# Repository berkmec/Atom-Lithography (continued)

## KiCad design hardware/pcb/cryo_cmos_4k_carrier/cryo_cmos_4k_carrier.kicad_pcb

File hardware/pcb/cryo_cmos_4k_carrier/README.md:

# Cryo-CMOS `4 K` Carrier (`968`-Gate SKY130 Crossbar Mux + `4 K / MXC` RC/Eccosorb Filter) & Live `ngspice-47` Verification

**BOM Coverage:** `S6.10-03`, `S6.7-02`, `S7.3-02`, `S7.3-01`  
**Epistemic Status:** `M0/M1_DESIGN_ONLY` — `no_lab_measurement=true`, `no_physical_fab=true`, `iec61508_certified=false`, `semi_s2_certified=false`. Active COTS connectors are `{Aday-COTS}`; SKY130 `4 K` dies and Eccosorb CR-124 RF absorber blocks are `{Ozel-Uretim}`.

## 1. `4 K` 4-Layer Cryo-CMOS Carrier Architecture (`cryo_cmos_4k_carrier.{kicad_sch,kicad_pcb}`)

- **Dimensions & Stackup:** `165 × 125 mm`, **`4` copper layers**, `1.478 mm` total thickness, thermal-cycle-hardened (`>100` cooldowns `300 K ↔ 4 K`):
  - Outer ENIG Au wire-bondable layers (`F.Cu`, `B.Cu`) over `0.254 mm` **Rogers RO4350B** (`ε_r = 3.48`).
  - Central `0.800 mm` **AlN / Cu-Invar-Cu CTE-matched core** (`ε_r = 8.90`, `CTE ≈ 4.5 ppm/K` matched to Si) sandwiched between `In1.Cu` (`GND_4K`) and `In2.Cu` (`VDD_4K_1V2`).
- **Thermal Isolation Split (`OBS-019`):** `4 K` (`GND_4K`, `x ≤ 112 mm`, `J_THERM_4K_A/B`) and `20 mK` MXC (`GND_MXC`, `x ≥ 118 mm`, `J_THERM_MXC`, `R2_MXC`/`C2_MXC`/`J_MXC_GATE_A/B`) copper planes are physically split across a `6.0 mm` copper-free thermal break moat (`5.0 mm` multi-layer `THERMAL_ISOLATION_4K_TO_MXC` keepout), eliminating the `~34.8 mW` unbroken copper plane thermal short; full dilution-fridge build mounts Stage-2 on a separate MXC daughterboard via NbTi/manganin Eccosorb harnesses.
- **`968`-Gate SKY130 `4 K` Crossbar Mux (`S6.10-03`, `S7.3-01`, `S7.3-02`, `OBS-091` / `OBS-135`):**
  - Hosts `8×` SKY130 `121`-gate cryo-CMOS crossbar mux dies (`U_MUX0..U_MUX7` = `968` local Stark/M4/SET DC gates for the `Exp131` `L = 11` surface code: `121` nodes × `8` DC gates/node; `8` representative bank outputs routed to the filter array).
  - Real `0.635 mm` pitch Omnetics Bi-Lobe Nano-D connectors (`Connector_Omnetics:NanoD_2x4_P0.635mm`, G-S-G-S high-speed pinout); per-chip `100 nF C0G/NP0` decoupling on ALL 3 rails (`VDD_4K_1V2`, `VBIAS_POS_2V`, `VBIAS_NEG_2V`; zero Class-II X7R freeze-out); SKY130 `±2.0 V` (`4.0 V` span) gate-hold buffers require `5 V` thick-oxide (`g5v0d10v5`) triple-well devices tied to `-2.0 V` and `4 K` BSIM4 PDK verification at M2 (`NMOS_SKY4K`/`PMOS_SKY4K` in SPICE are `LEVEL=1` behavioral effective-`V_th` switches).
  - Controlled `50 Ω SE` SPI microstrips across ALL SPI nets INCLUDING daisy-chain hops `SPI_CHAIN_0_1..6_7` (`w = 0.5429 mm` → `Z0 = 50.00 Ω`, `193 / 193` DRC checks PASS, adjacent `GND_4K` stitching vias `< 3.5 mm` from every die).
- **`4 K / MXC (20 mK)` 2-Stage RC + Eccosorb CR-124 DC Gate Filter Bank (`S6.7-02`):**
  - `8` representative Stark/M4/SET filter channels (`R1 = 1.0 kΩ` NiCr + `C1 = 100 nF` C0G `|| 100 pF` HF shunt w/ `1.0 Ω` NiCr ESL-damping ESR at `4 K` → `Eccosorb CR-124` → `6.0 mm` thermal moat → `R2 = 2.0 kΩ` + `C2 = 47 nF` C0G `|| 100 pF` HF shunt on isolated `GND_MXC` at `20 mK`).
- **Strict EDA & Physical Copper Connectivity Verification:** `100` components, `54` nets, **`routed = 54 / 54` (`100%` pad-to-pad)**, **`unconnected_items = 0`**, **`track_dangling_count = 0`**, `782` copper segments, `251` vias, **`0` ERC errors**, **`0` DRC errors**, `SCH ↔ PCB` netlist parity PASS.

## 2. Live `ngspice-47` `4 K / 20 mK` Filter, Thermal Noise & Power Verification (`cryo_4k_gate_filter.cir`)

Executed natively with `ngspice-47 -b` (exit `0`, `0` errors, `0` warnings) using `.temp -269.15` (`4.00 K` global stage), per-instance `temp=-273.13` (`20 mK` MXC), and `temp=26.85` (`300 K` upstream DAC noise equivalent `7.50 nV/√Hz`), including realistic `0.05 pF` resistor body strays, `0.60 nH` MLCC ESLs with `1.0 Ω` HF damping ESR, and FULL bipolar `±2.0 V` (`+2.0 V` AND `-2.0 V` rail) power accounting:

| Metric | `ngspice-47` Measured | Independent Python MNA / Nyquist | Target / Spec | Status |
| :--- | :---: | :---: | :---: | :---: |
| Filter `-3 dB` Bandwidth `f_3dB` | `669.29 Hz` | — | Quasi-static DC Stark/SET | **PASS** |
| RF Attenuation `@ 1 GHz` (w/ `1.0 Ω` ESL damping) | **`-172.82 dB`** | `-172.83 dB` (`0.009 dB` diff) | `> 60 dB` (`≤ -60 dB`) | **PASS** |
| In-Band Total Noise `@ 10 Hz` (`300 K` DAC + `4 K` + `20 mK`) | **`7.523 nV/√Hz`** (`0.00752 µV/√Hz`) | `7.524 nV/√Hz` (`0.01%` parity) | `< 0.5 µV/√Hz` | **PASS** |
| Intrinsic `4 K + 20 mK` Filter-Only Thermal Noise `@ 10 Hz` | **`0.5275 nV/√Hz`** | `0.5276 nV/√Hz` (`0.02%` parity) | Cryogenic Nyquist floor | **PASS** |
| Total Integrated Output RMS Noise (`1 Hz – 1 MHz`) | **`0.2251 µVrms`** | — | Sub-µVrms Stark/SET stability | **PASS** |
| `0 → 1.0 V` Stark Step `10–90%` Rise / `0.1%` Settling Time | `520.2 µs` / **`1.632 ms`** | — | Clean settling `< 5 ms` | **PASS** |
| `968`-Gate SKY130 `4 K` Total Power (incl. `+2 V` & `-2 V` rails) | **`13.636 mW`** (`2.808` core/dyn + `5.414` `+2 V` + `5.414` `-2 V`) | — | **`≤ 15.4 mW @ 4 K`** | **PASS** |

*\*Epistemic caveat:* Lumped SPICE models assume an ideal Faraday partition between the `4 K` and `20 mK` filter bays; physical cryogenic enclosure cavity crosstalk typically floors practical measured RF isolation near `100–120 dB`, still providing `40–60 dB` margin beyond the `> 60 dB @ 1 GHz` requirement.

## 3. Reproducibility

```bash
PYTHONPATH=.:src python -B hardware/pcb/cryo_cmos_4k_carrier/build_cryo_4k_carrier.py
PYTHONPATH=.:src pytest tests/test_pcb_fpga_blanker_cryo.py -v -p no:cacheprovider
```

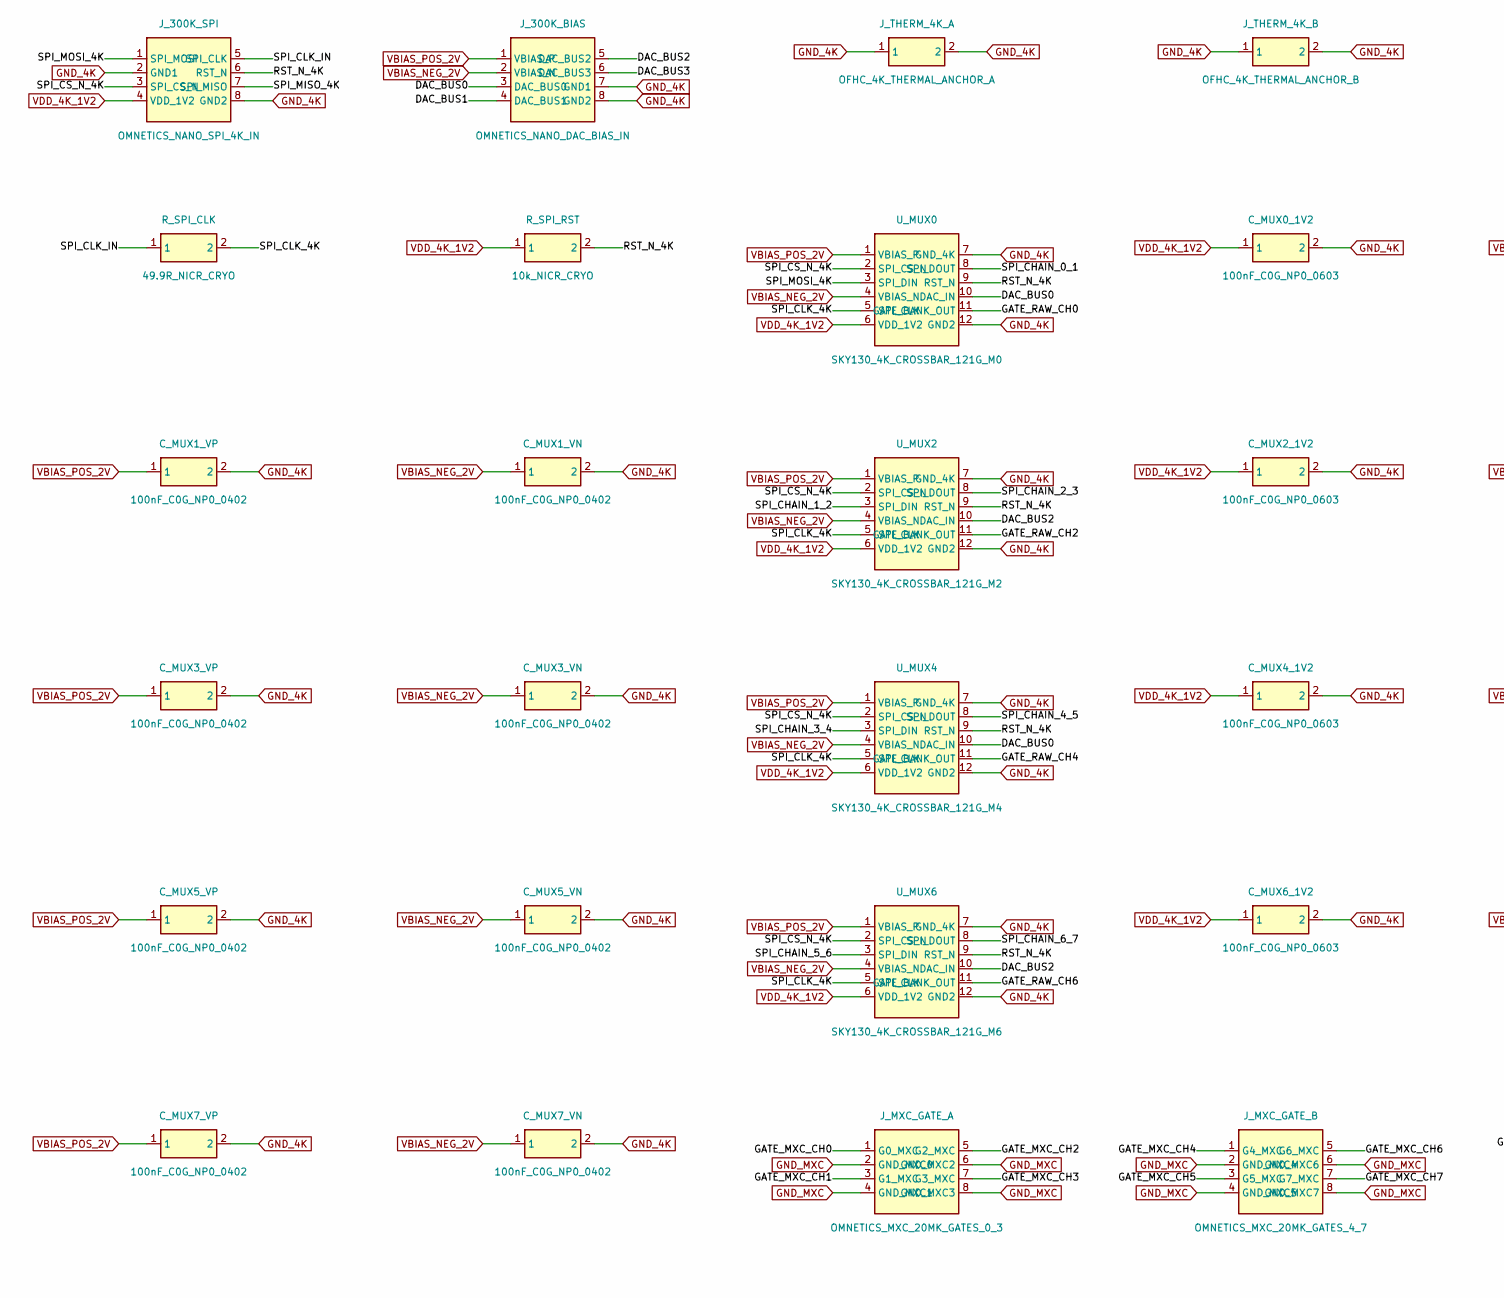
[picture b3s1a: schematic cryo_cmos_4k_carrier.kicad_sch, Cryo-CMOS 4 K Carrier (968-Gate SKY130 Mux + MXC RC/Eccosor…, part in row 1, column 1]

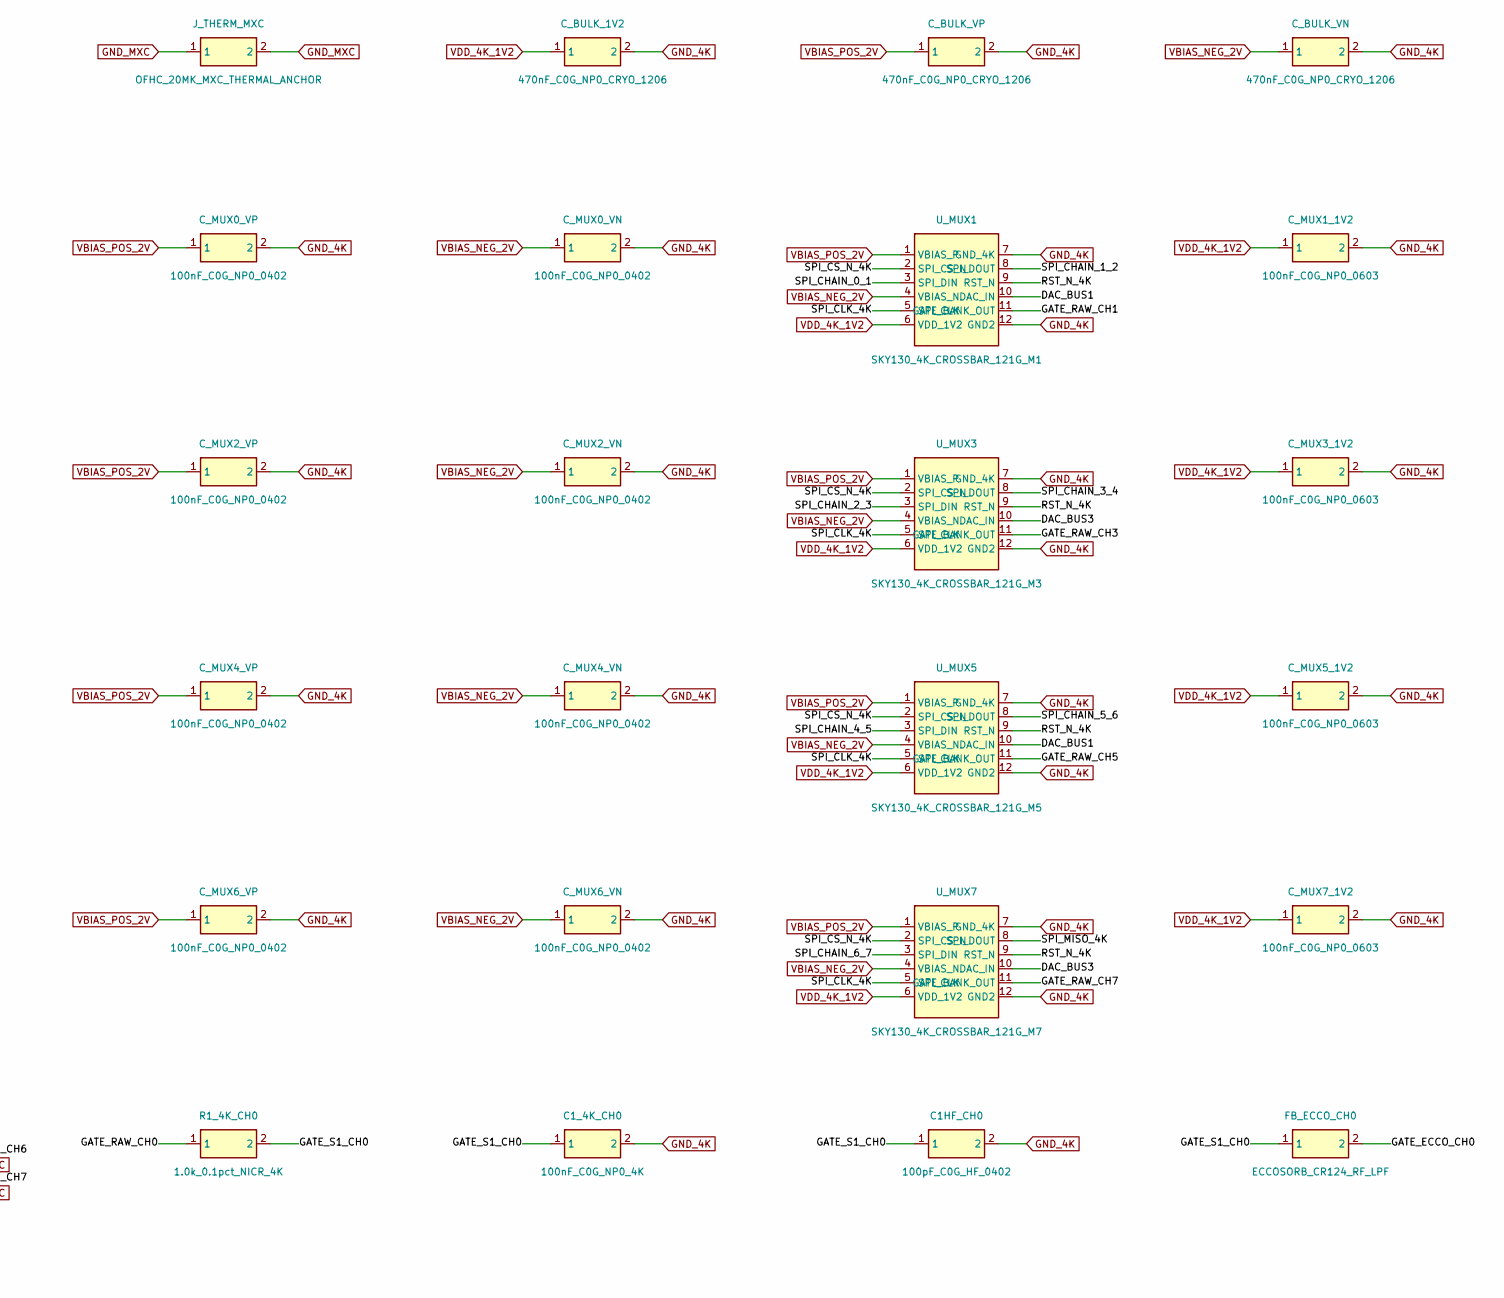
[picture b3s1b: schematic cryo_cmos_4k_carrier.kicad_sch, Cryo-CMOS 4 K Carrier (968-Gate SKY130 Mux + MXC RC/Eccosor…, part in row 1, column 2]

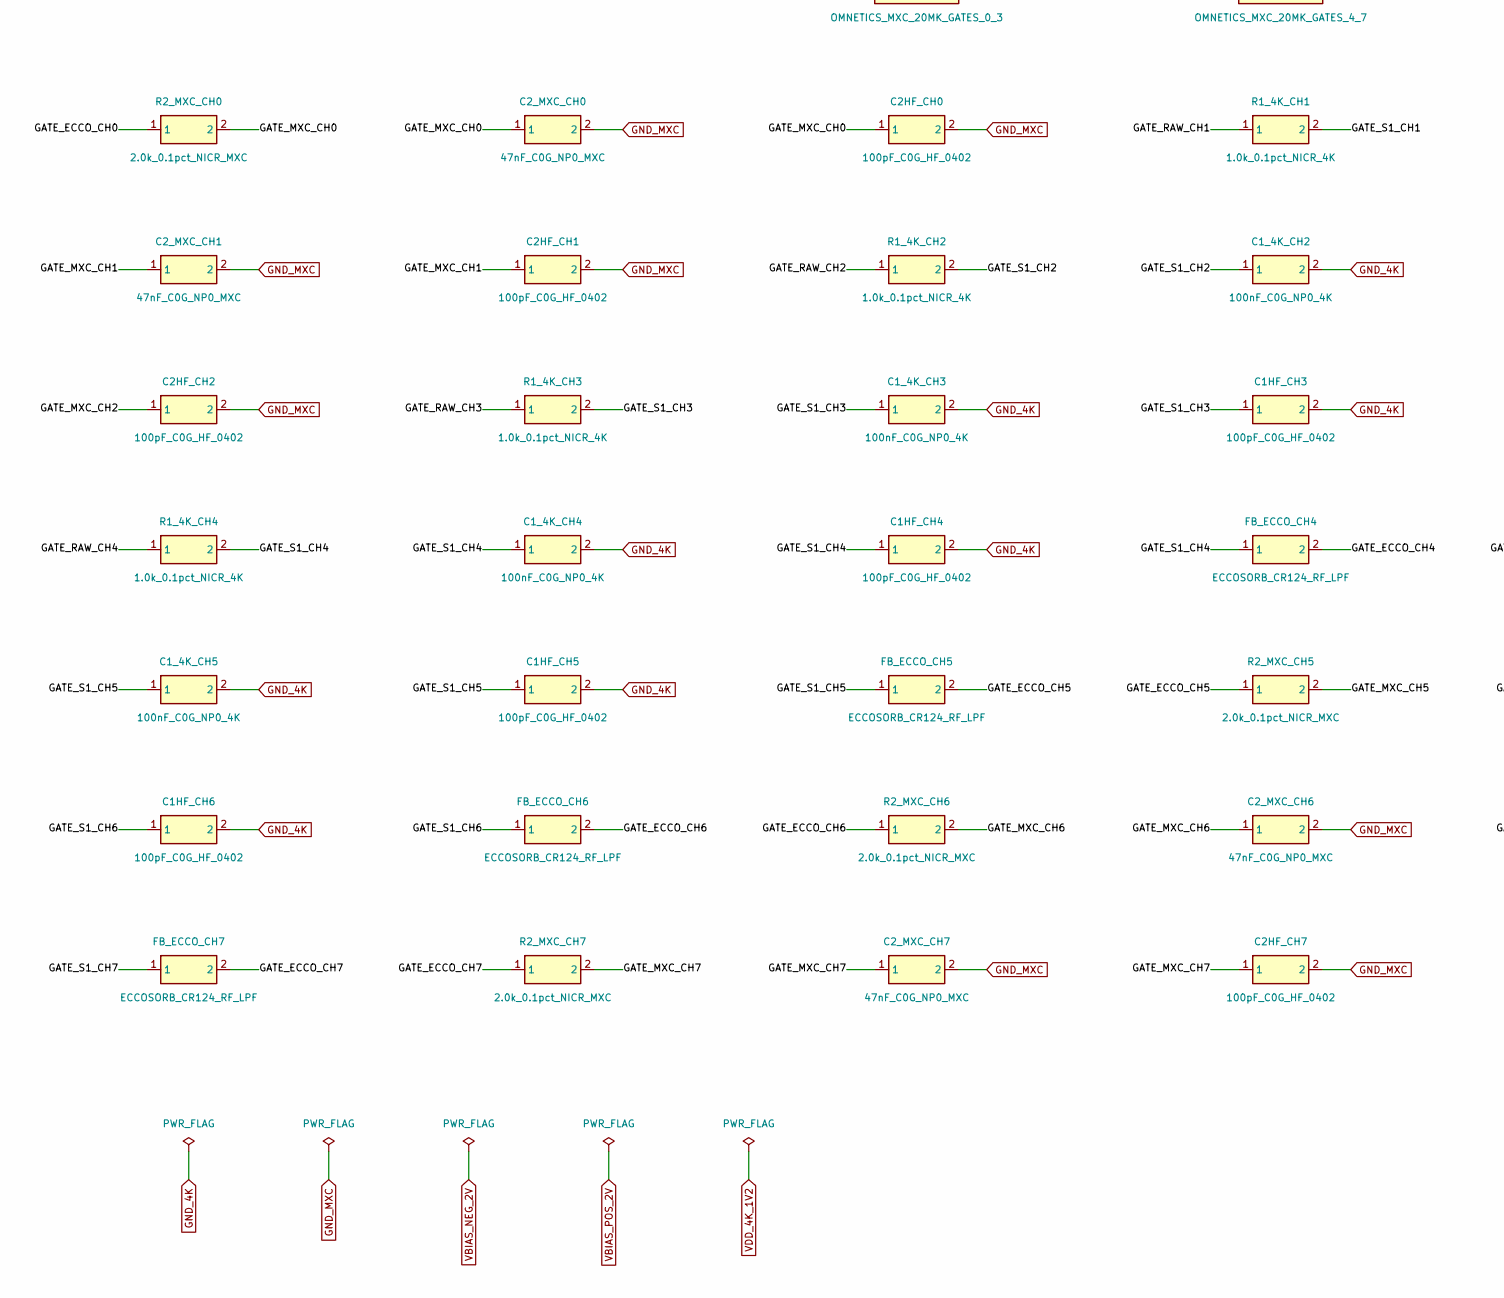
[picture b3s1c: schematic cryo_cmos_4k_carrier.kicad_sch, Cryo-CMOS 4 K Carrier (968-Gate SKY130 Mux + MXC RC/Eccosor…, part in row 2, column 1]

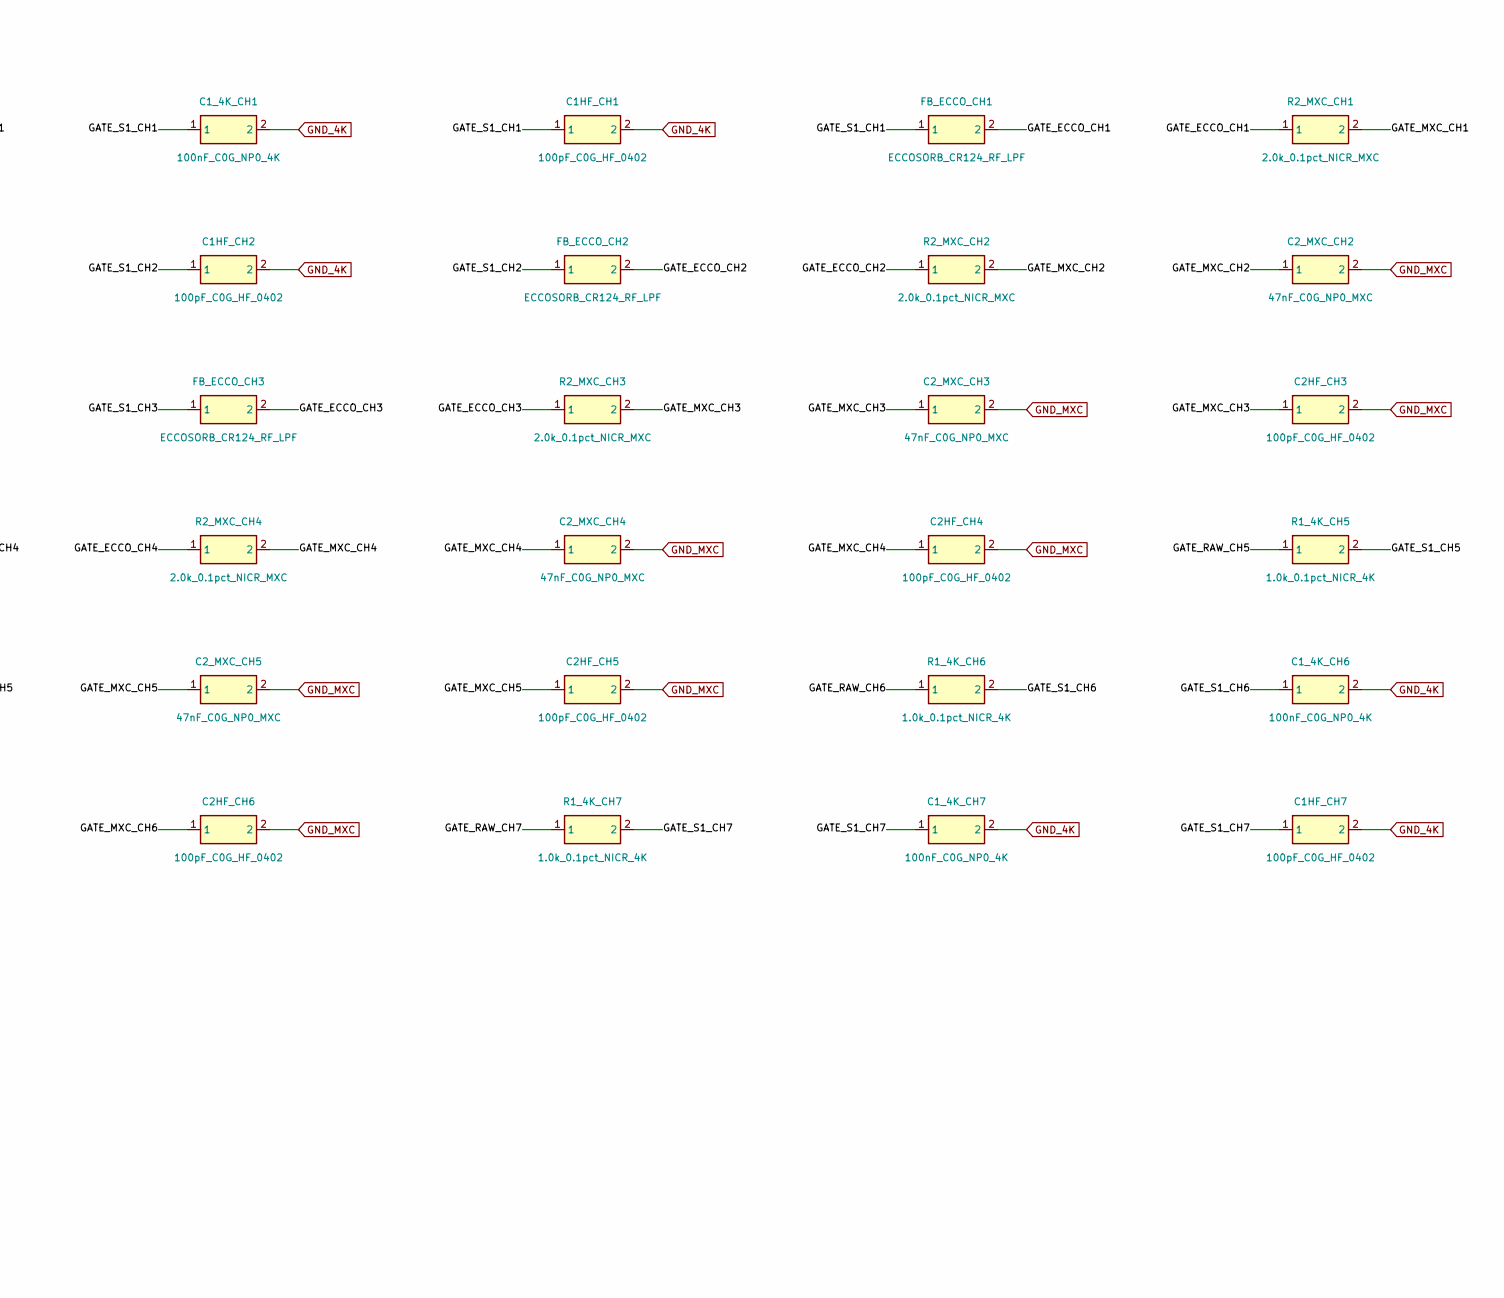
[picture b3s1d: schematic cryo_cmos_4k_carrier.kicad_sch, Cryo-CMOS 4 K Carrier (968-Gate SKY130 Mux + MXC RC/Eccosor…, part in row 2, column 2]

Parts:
C1HF_CH0, C1HF_CH1, C1HF_CH2, C1HF_CH3, C1HF_CH4, C1HF_CH5, C1HF_CH6, C1HF_CH7, C2HF_CH0, C2HF_CH1, C2HF_CH2, C2HF_CH3, C2HF_CH4, C2HF_CH5, C2HF_CH6, C2HF_CH7: 100pF_C0G_HF_0402; C_0402_1005Metric; MPN 100pF_C0G_HF_0402
C1_4K_CH0, C1_4K_CH1, C1_4K_CH2, C1_4K_CH3, C1_4K_CH4, C1_4K_CH5, C1_4K_CH6, C1_4K_CH7: 100nF_C0G_NP0_4K; C_0805_2012Metric; MPN 100nF_C0G_NP0_4K
C2_MXC_CH0, C2_MXC_CH1, C2_MXC_CH2, C2_MXC_CH3, C2_MXC_CH4, C2_MXC_CH5, C2_MXC_CH6, C2_MXC_CH7: 47nF_C0G_NP0_MXC; C_0805_2012Metric; MPN 47nF_C0G_NP0_MXC
C_BULK_1V2: 470nF_C0G_NP0_CRYO_1206; C_1206_3216Metric; MPN 470nF_C0G_NP0_CRYO_1206
C_BULK_VN: 470nF_C0G_NP0_CRYO_1206; C_1206_3216Metric; MPN 470nF_C0G_NP0_CRYO_1206
C_BULK_VP: 470nF_C0G_NP0_CRYO_1206; C_1206_3216Metric; MPN 470nF_C0G_NP0_CRYO_1206
C_MUX0_1V2, C_MUX1_1V2, C_MUX2_1V2, C_MUX3_1V2, C_MUX4_1V2, C_MUX5_1V2, C_MUX6_1V2, C_MUX7_1V2: 100nF_C0G_NP0_0603; C_0603_1608Metric; MPN 100nF_C0G_NP0_0603
C_MUX0_VN, C_MUX0_VP, C_MUX1_VN, C_MUX1_VP, C_MUX2_VN, C_MUX2_VP, C_MUX3_VN, C_MUX3_VP, C_MUX4_VN, C_MUX4_VP, C_MUX5_VN, C_MUX5_VP, C_MUX6_VN, C_MUX6_VP, C_MUX7_VN, C_MUX7_VP: 100nF_C0G_NP0_0402; C_0402_1005Metric; MPN 100nF_C0G_NP0_0402
FB_ECCO_CH0, FB_ECCO_CH1, FB_ECCO_CH2, FB_ECCO_CH3, FB_ECCO_CH4, FB_ECCO_CH5, FB_ECCO_CH6, FB_ECCO_CH7: ECCOSORB_CR124_RF_LPF; L_1206_3216Metric; MPN ECCOSORB_CR124_RF_LPF
J_300K_BIAS: OMNETICS_NANO_DAC_BIAS_IN; NanoD_2x4_P0.635mm; MPN A79040-001
J_300K_SPI: OMNETICS_NANO_SPI_4K_IN; NanoD_2x4_P0.635mm; MPN A79040-001
J_MXC_GATE_A: OMNETICS_MXC_20MK_GATES_0_3; NanoD_2x4_P0.635mm; MPN A79040-001
J_MXC_GATE_B: OMNETICS_MXC_20MK_GATES_4_7; NanoD_2x4_P0.635mm; MPN A79040-001
J_THERM_4K_A: OFHC_4K_THERMAL_ANCHOR_A; HDR_1x2_2.54mm; MPN OFHC_4K_THERMAL_ANCHOR_A
J_THERM_4K_B: OFHC_4K_THERMAL_ANCHOR_B; HDR_1x2_2.54mm; MPN OFHC_4K_THERMAL_ANCHOR_B
J_THERM_MXC: OFHC_20MK_MXC_THERMAL_ANCHOR; HDR_1x2_2.54mm; MPN OFHC_20MK_MXC_THERMAL_ANCHOR
R1_4K_CH0, R1_4K_CH1, R1_4K_CH2, R1_4K_CH3, R1_4K_CH4, R1_4K_CH5, R1_4K_CH6, R1_4K_CH7: 1.0k_0.1pct_NICR_4K; R_0603_1608Metric; MPN 1.0k_0.1pct_NICR_4K
R2_MXC_CH0, R2_MXC_CH1, R2_MXC_CH2, R2_MXC_CH3, R2_MXC_CH4, R2_MXC_CH5, R2_MXC_CH6, R2_MXC_CH7: 2.0k_0.1pct_NICR_MXC; R_0603_1608Metric; MPN 2.0k_0.1pct_NICR_MXC
R_SPI_CLK: 49.9R_NICR_CRYO; R_0603_1608Metric; MPN 49.9R_NICR_CRYO
R_SPI_RST: 10k_NICR_CRYO; R_0603_1608Metric; MPN 10k_NICR_CRYO
U_MUX0: SKY130_4K_CROSSBAR_121G_M0; SKY130_CRYO_CARRIER_12P; MPN SKY130-CRYO-MUX121-4K
U_MUX1: SKY130_4K_CROSSBAR_121G_M1; SKY130_CRYO_CARRIER_12P; MPN SKY130-CRYO-MUX121-4K
U_MUX2: SKY130_4K_CROSSBAR_121G_M2; SKY130_CRYO_CARRIER_12P; MPN SKY130-CRYO-MUX121-4K
U_MUX3: SKY130_4K_CROSSBAR_121G_M3; SKY130_CRYO_CARRIER_12P; MPN SKY130-CRYO-MUX121-4K
U_MUX4: SKY130_4K_CROSSBAR_121G_M4; SKY130_CRYO_CARRIER_12P; MPN SKY130-CRYO-MUX121-4K
U_MUX5: SKY130_4K_CROSSBAR_121G_M5; SKY130_CRYO_CARRIER_12P; MPN SKY130-CRYO-MUX121-4K
U_MUX6: SKY130_4K_CROSSBAR_121G_M6; SKY130_CRYO_CARRIER_12P; MPN SKY130-CRYO-MUX121-4K
U_MUX7: SKY130_4K_CROSSBAR_121G_M7; SKY130_CRYO_CARRIER_12P; MPN SKY130-CRYO-MUX121-4K

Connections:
DAC_BUS0: J_300K_BIAS.3 (DAC_BUS0), U_MUX0.10 (DAC_IN), U_MUX4.10 (DAC_IN)
DAC_BUS1: J_300K_BIAS.4 (DAC_BUS1), U_MUX1.10 (DAC_IN), U_MUX5.10 (DAC_IN)
DAC_BUS2: J_300K_BIAS.5 (DAC_BUS2), U_MUX2.10 (DAC_IN), U_MUX6.10 (DAC_IN)
DAC_BUS3: J_300K_BIAS.6 (DAC_BUS3), U_MUX3.10 (DAC_IN), U_MUX7.10 (DAC_IN)
GATE_ECCO_CH0: FB_ECCO_CH0.2, R2_MXC_CH0.1
GATE_ECCO_CH1: FB_ECCO_CH1.2, R2_MXC_CH1.1
GATE_ECCO_CH2: FB_ECCO_CH2.2, R2_MXC_CH2.1
GATE_ECCO_CH3: FB_ECCO_CH3.2, R2_MXC_CH3.1
GATE_ECCO_CH4: FB_ECCO_CH4.2, R2_MXC_CH4.1
GATE_ECCO_CH5: FB_ECCO_CH5.2, R2_MXC_CH5.1
GATE_ECCO_CH6: FB_ECCO_CH6.2, R2_MXC_CH6.1
GATE_ECCO_CH7: FB_ECCO_CH7.2, R2_MXC_CH7.1
GATE_MXC_CH0: C2HF_CH0.1, C2_MXC_CH0.1, J_MXC_GATE_A.1 (G0_MXC), R2_MXC_CH0.2
GATE_MXC_CH1: C2HF_CH1.1, C2_MXC_CH1.1, J_MXC_GATE_A.3 (G1_MXC), R2_MXC_CH1.2
GATE_MXC_CH2: C2HF_CH2.1, C2_MXC_CH2.1, J_MXC_GATE_A.5 (G2_MXC), R2_MXC_CH2.2
GATE_MXC_CH3: C2HF_CH3.1, C2_MXC_CH3.1, J_MXC_GATE_A.7 (G3_MXC), R2_MXC_CH3.2
GATE_MXC_CH4: C2HF_CH4.1, C2_MXC_CH4.1, J_MXC_GATE_B.1 (G4_MXC), R2_MXC_CH4.2
GATE_MXC_CH5: C2HF_CH5.1, C2_MXC_CH5.1, J_MXC_GATE_B.3 (G5_MXC), R2_MXC_CH5.2
GATE_MXC_CH6: C2HF_CH6.1, C2_MXC_CH6.1, J_MXC_GATE_B.5 (G6_MXC), R2_MXC_CH6.2
GATE_MXC_CH7: C2HF_CH7.1, C2_MXC_CH7.1, J_MXC_GATE_B.7 (G7_MXC), R2_MXC_CH7.2
GATE_RAW_CH0: R1_4K_CH0.1, U_MUX0.11 (GATE_BANK_OUT)
GATE_RAW_CH1: R1_4K_CH1.1, U_MUX1.11 (GATE_BANK_OUT)
GATE_RAW_CH2: R1_4K_CH2.1, U_MUX2.11 (GATE_BANK_OUT)
GATE_RAW_CH3: R1_4K_CH3.1, U_MUX3.11 (GATE_BANK_OUT)
GATE_RAW_CH4: R1_4K_CH4.1, U_MUX4.11 (GATE_BANK_OUT)
GATE_RAW_CH5: R1_4K_CH5.1, U_MUX5.11 (GATE_BANK_OUT)
GATE_RAW_CH6: R1_4K_CH6.1, U_MUX6.11 (GATE_BANK_OUT)
GATE_RAW_CH7: R1_4K_CH7.1, U_MUX7.11 (GATE_BANK_OUT)
GATE_S1_CH0: C1HF_CH0.1, C1_4K_CH0.1, FB_ECCO_CH0.1, R1_4K_CH0.2
GATE_S1_CH1: C1HF_CH1.1, C1_4K_CH1.1, FB_ECCO_CH1.1, R1_4K_CH1.2
GATE_S1_CH2: C1HF_CH2.1, C1_4K_CH2.1, FB_ECCO_CH2.1, R1_4K_CH2.2
GATE_S1_CH3: C1HF_CH3.1, C1_4K_CH3.1, FB_ECCO_CH3.1, R1_4K_CH3.2
GATE_S1_CH4: C1HF_CH4.1, C1_4K_CH4.1, FB_ECCO_CH4.1, R1_4K_CH4.2
GATE_S1_CH5: C1HF_CH5.1, C1_4K_CH5.1, FB_ECCO_CH5.1, R1_4K_CH5.2
GATE_S1_CH6: C1HF_CH6.1, C1_4K_CH6.1, FB_ECCO_CH6.1, R1_4K_CH6.2
GATE_S1_CH7: C1HF_CH7.1, C1_4K_CH7.1, FB_ECCO_CH7.1, R1_4K_CH7.2
GND_4K: C1HF_CH0.2, C1HF_CH1.2, C1HF_CH2.2, C1HF_CH3.2, C1HF_CH4.2, C1HF_CH5.2, C1HF_CH6.2, C1HF_CH7.2, C1_4K_CH0.2, C1_4K_CH1.2, C1_4K_CH2.2, C1_4K_CH3.2, C1_4K_CH4.2, C1_4K_CH5.2, C1_4K_CH6.2, C1_4K_CH7.2, C_BULK_1V2.2, C_BULK_VN.2, C_BULK_VP.2, C_MUX0_1V2.2, C_MUX0_VN.2, C_MUX0_VP.2, C_MUX1_1V2.2, C_MUX1_VN.2, C_MUX1_VP.2, C_MUX2_1V2.2, C_MUX2_VN.2, C_MUX2_VP.2, C_MUX3_1V2.2, C_MUX3_VN.2, C_MUX3_VP.2, C_MUX4_1V2.2, C_MUX4_VN.2, C_MUX4_VP.2, C_MUX5_1V2.2, C_MUX5_VN.2, C_MUX5_VP.2, C_MUX6_1V2.2, C_MUX6_VN.2, C_MUX6_VP.2, C_MUX7_1V2.2, C_MUX7_VN.2, C_MUX7_VP.2, J_300K_BIAS.7 (GND1), J_300K_BIAS.8 (GND2), J_300K_SPI.2 (GND1), J_300K_SPI.8 (GND2), J_THERM_4K_A.1, J_THERM_4K_A.2, J_THERM_4K_B.1, J_THERM_4K_B.2, U_MUX0.7 (GND_4K), U_MUX0.12 (GND2), U_MUX1.7 (GND_4K), U_MUX1.12 (GND2), U_MUX2.7 (GND_4K), U_MUX2.12 (GND2), U_MUX3.7 (GND_4K), U_MUX3.12 (GND2), U_MUX4.7 (GND_4K), U_MUX4.12 (GND2), U_MUX5.7 (GND_4K), U_MUX5.12 (GND2), U_MUX6.7 (GND_4K), U_MUX6.12 (GND2), U_MUX7.7 (GND_4K), U_MUX7.12 (GND2)
GND_MXC: C2HF_CH0.2, C2HF_CH1.2, C2HF_CH2.2, C2HF_CH3.2, C2HF_CH4.2, C2HF_CH5.2, C2HF_CH6.2, C2HF_CH7.2, C2_MXC_CH0.2, C2_MXC_CH1.2, C2_MXC_CH2.2, C2_MXC_CH3.2, C2_MXC_CH4.2, C2_MXC_CH5.2, C2_MXC_CH6.2, C2_MXC_CH7.2, J_MXC_GATE_A.2 (GND_MXC0), J_MXC_GATE_A.4 (GND_MXC1), J_MXC_GATE_A.6 (GND_MXC2), J_MXC_GATE_A.8 (GND_MXC3), J_MXC_GATE_B.2 (GND_MXC4), J_MXC_GATE_B.4 (GND_MXC5), J_MXC_GATE_B.6 (GND_MXC6), J_MXC_GATE_B.8 (GND_MXC7), J_THERM_MXC.1, J_THERM_MXC.2
RST_N_4K: J_300K_SPI.6 (RST_N), R_SPI_RST.2, U_MUX0.9 (RST_N), U_MUX1.9 (RST_N), U_MUX2.9 (RST_N), U_MUX3.9 (RST_N), U_MUX4.9 (RST_N), U_MUX5.9 (RST_N), U_MUX6.9 (RST_N), U_MUX7.9 (RST_N)
SPI_CHAIN_0_1: U_MUX0.8 (SPI_DOUT), U_MUX1.3 (SPI_DIN)
SPI_CHAIN_1_2: U_MUX1.8 (SPI_DOUT), U_MUX2.3 (SPI_DIN)
SPI_CHAIN_2_3: U_MUX2.8 (SPI_DOUT), U_MUX3.3 (SPI_DIN)
SPI_CHAIN_3_4: U_MUX3.8 (SPI_DOUT), U_MUX4.3 (SPI_DIN)
SPI_CHAIN_4_5: U_MUX4.8 (SPI_DOUT), U_MUX5.3 (SPI_DIN)
SPI_CHAIN_5_6: U_MUX5.8 (SPI_DOUT), U_MUX6.3 (SPI_DIN)
SPI_CHAIN_6_7: U_MUX6.8 (SPI_DOUT), U_MUX7.3 (SPI_DIN)
SPI_CLK_4K: R_SPI_CLK.2, U_MUX0.5 (SPI_CLK), U_MUX1.5 (SPI_CLK), U_MUX2.5 (SPI_CLK), U_MUX3.5 (SPI_CLK), U_MUX4.5 (SPI_CLK), U_MUX5.5 (SPI_CLK), U_MUX6.5 (SPI_CLK), U_MUX7.5 (SPI_CLK)
SPI_CLK_IN: J_300K_SPI.5 (SPI_CLK), R_SPI_CLK.1
SPI_CS_N_4K: J_300K_SPI.3 (SPI_CS_N), U_MUX0.2 (SPI_CS_N), U_MUX1.2 (SPI_CS_N), U_MUX2.2 (SPI_CS_N), U_MUX3.2 (SPI_CS_N), U_MUX4.2 (SPI_CS_N), U_MUX5.2 (SPI_CS_N), U_MUX6.2 (SPI_CS_N), U_MUX7.2 (SPI_CS_N)
SPI_MISO_4K: J_300K_SPI.7 (SPI_MISO), U_MUX7.8 (SPI_DOUT)
SPI_MOSI_4K: J_300K_SPI.1 (SPI_MOSI), U_MUX0.3 (SPI_DIN)
VBIAS_NEG_2V: C_BULK_VN.1, C_MUX0_VN.1, C_MUX1_VN.1, C_MUX2_VN.1, C_MUX3_VN.1, C_MUX4_VN.1, C_MUX5_VN.1, C_MUX6_VN.1, C_MUX7_VN.1, J_300K_BIAS.2 (VBIAS_N), U_MUX0.4 (VBIAS_N), U_MUX1.4 (VBIAS_N), U_MUX2.4 (VBIAS_N), U_MUX3.4 (VBIAS_N), U_MUX4.4 (VBIAS_N), U_MUX5.4 (VBIAS_N), U_MUX6.4 (VBIAS_N), U_MUX7.4 (VBIAS_N)
VBIAS_POS_2V: C_BULK_VP.1, C_MUX0_VP.1, C_MUX1_VP.1, C_MUX2_VP.1, C_MUX3_VP.1, C_MUX4_VP.1, C_MUX5_VP.1, C_MUX6_VP.1, C_MUX7_VP.1, J_300K_BIAS.1 (VBIAS_P), U_MUX0.1 (VBIAS_P), U_MUX1.1 (VBIAS_P), U_MUX2.1 (VBIAS_P), U_MUX3.1 (VBIAS_P), U_MUX4.1 (VBIAS_P), U_MUX5.1 (VBIAS_P), U_MUX6.1 (VBIAS_P), U_MUX7.1 (VBIAS_P)
VDD_4K_1V2: C_BULK_1V2.1, C_MUX0_1V2.1, C_MUX1_1V2.1, C_MUX2_1V2.1, C_MUX3_1V2.1, C_MUX4_1V2.1, C_MUX5_1V2.1, C_MUX6_1V2.1, C_MUX7_1V2.1, J_300K_SPI.4 (VDD_1V2), R_SPI_RST.1, U_MUX0.6 (VDD_1V2), U_MUX1.6 (VDD_1V2), U_MUX2.6 (VDD_1V2), U_MUX3.6 (VDD_1V2), U_MUX4.6 (VDD_1V2), U_MUX5.6 (VDD_1V2), U_MUX6.6 (VDD_1V2), U_MUX7.6 (VDD_1V2)

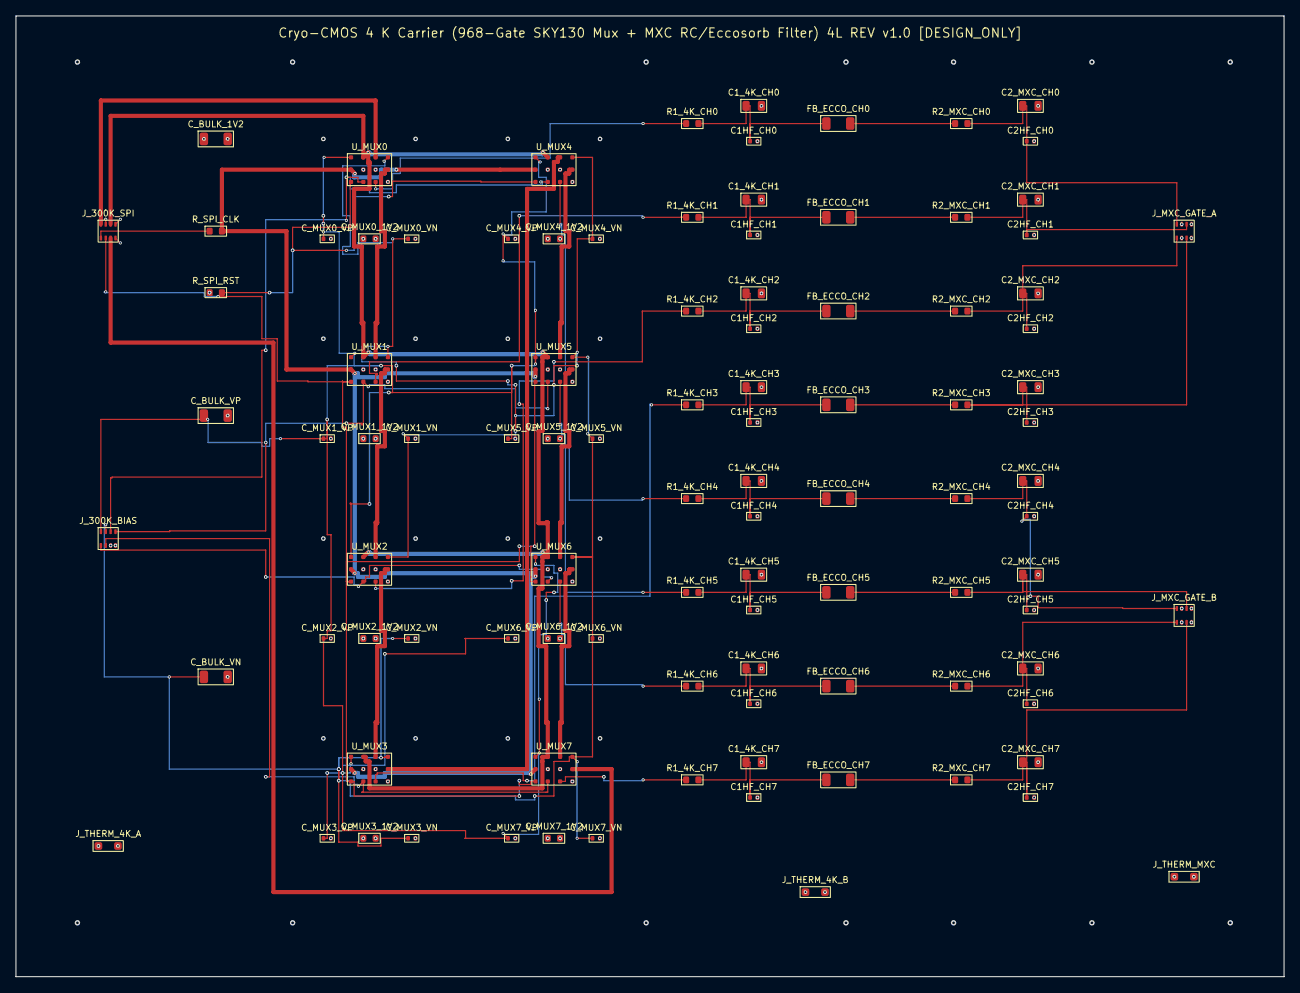
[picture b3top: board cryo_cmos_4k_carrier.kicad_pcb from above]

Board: 4 copper layers, 165.0 x 125.0 mm, 100 parts (0 on the bottom side), 54 nets.
